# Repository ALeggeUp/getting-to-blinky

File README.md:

# Getting to Blinky

# License

This work is licensed under the Creative Commons Attribution 4.0 International License. To view a copy of this license, visit http://creativecommons.org/licenses/by/4.0/ or send a letter to Creative Commons, PO Box 1866, Mountain View, CA 94042, USA.

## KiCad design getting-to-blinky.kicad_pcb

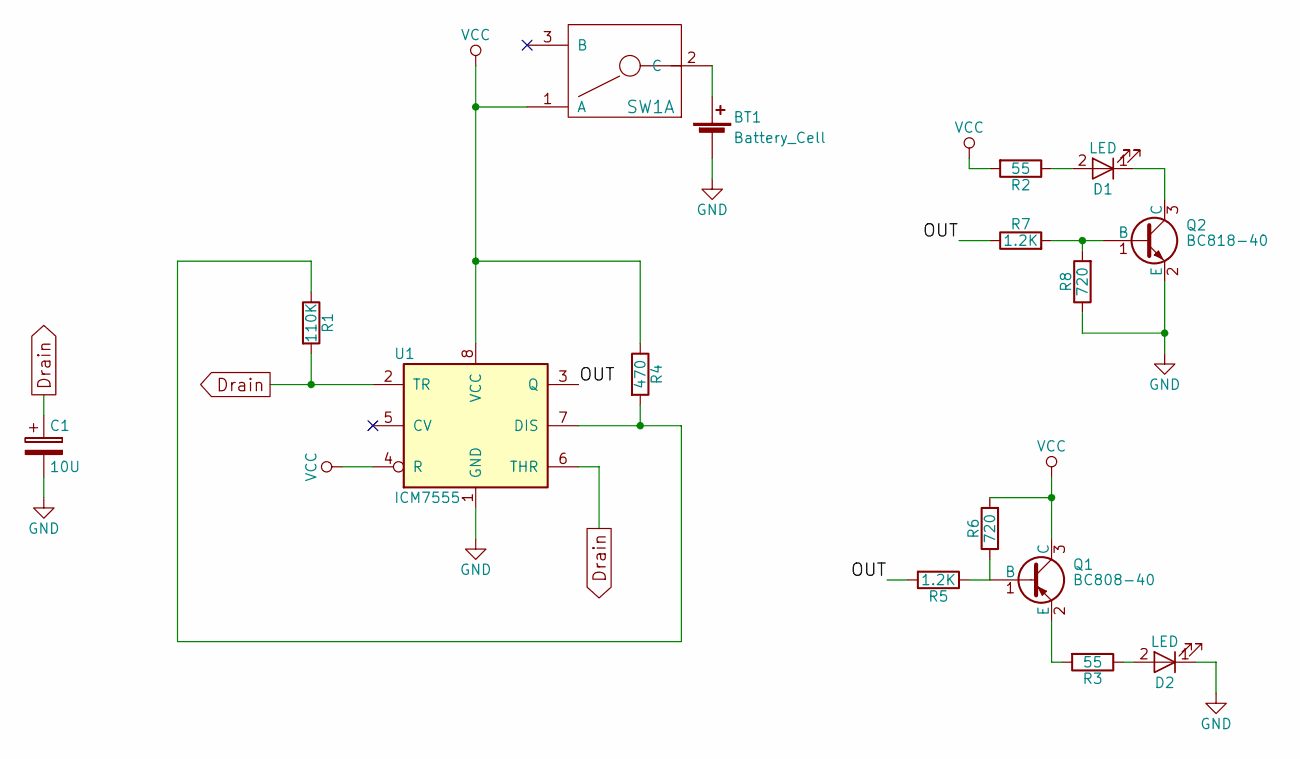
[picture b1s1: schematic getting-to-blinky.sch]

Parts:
BT1: Battery_Cell; BAT-HLD-001-CR2032
C1: 10U; CP_Tantalum_Case-A_EIA-3216-18_Hand
D1, D2: LED; LED_0805
Q1: BC808-40; SOT-23
Q2: BC818-40; SOT-23
R1: 110K; R_0805_HandSoldering
R2, R3: 55; R_0805_HandSoldering
R4: 470; R_0805_HandSoldering
R5, R7: 1.2K; R_0805_HandSoldering
R6, R8: 720; R_0805_HandSoldering
SW1: JS202011SCQN; MPN JS202011SCQN; Digikey Part 401-2002-1-ND
U1: ICM7555; SOIC-8_3.9x4.9mm_Pitch1.27mm

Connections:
/OUT: R5.2, R7.1, U1.3 (Q)
Drain: C1.1, R1.2, U1.2 (TR), U1.6 (THR)
GND: BT1.2 (-), C1.2, D2.1 (K), Q2.2 (E), R8.1, U1.1 (GND)
unnamed: BT1.1 (+), SW1.2 (C)
unnamed: D1.1 (K), Q2.3 (C)
unnamed: D1.2 (A), R2.1
unnamed: D2.2 (A), R3.1
unnamed: Q1.1 (B), R5.1, R6.1
unnamed: Q1.2 (E), R3.2
unnamed: Q2.1 (B), R7.2, R8.2
unnamed: R1.1, R4.2, U1.7 (DIS)
VCC: Q1.3 (C), R2.2, R4.1, R6.2, SW1.1 (A), U1.4 (R), U1.8 (VCC)

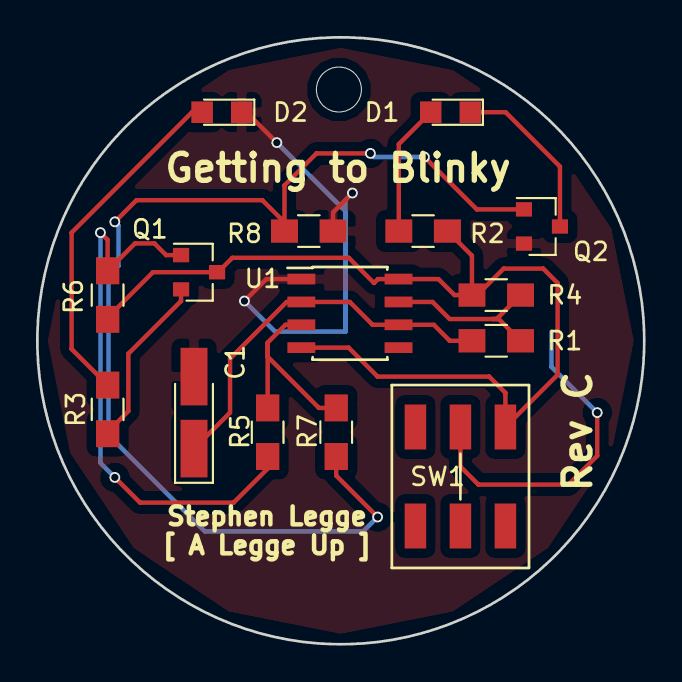
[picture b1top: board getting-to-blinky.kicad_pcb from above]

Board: 2 copper layers, 33.7 x 33.7 mm, 17 parts (1 on the bottom side), 12 nets.

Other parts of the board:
HOLE: MountingHole_2.5mm

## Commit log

2017-05-15 Add CC Attribution-ShareAlike 4.0 International information
2017-05-15 Snapshot of current project folder as of Rev B
2017-05-15 Gerber files are for Rev A, haven't created gerbers for Rev B yet
2017-05-15 Added image of latest board 3d render to README.md
2017-05-31 Update values for components
2017-05-31 Update with corrected battery polarity and added GND and VCC planes
2017-06-07 Falstad simulation of modified blinky circuit with transistors
2017-06-07 Re-worked blinky circuit with transistors due to limits of the 7555
2017-06-08 Finalized and cleaned up the schematic and layed out Rev C
2017-06-08 Add image of Rev C and update README.md with the latest
2017-06-08 Luckily caught the pads mask clearance before ordering
2017-06-15 Added parts for the new transistors
2017-07-03 Fill in some missing information for the BOM
